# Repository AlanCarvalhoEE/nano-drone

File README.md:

# Nano Drone
NanoDrone is a very small drone, aimed to be very simple and cheap to build.
The project is under development and the first version should be manufactured soon.

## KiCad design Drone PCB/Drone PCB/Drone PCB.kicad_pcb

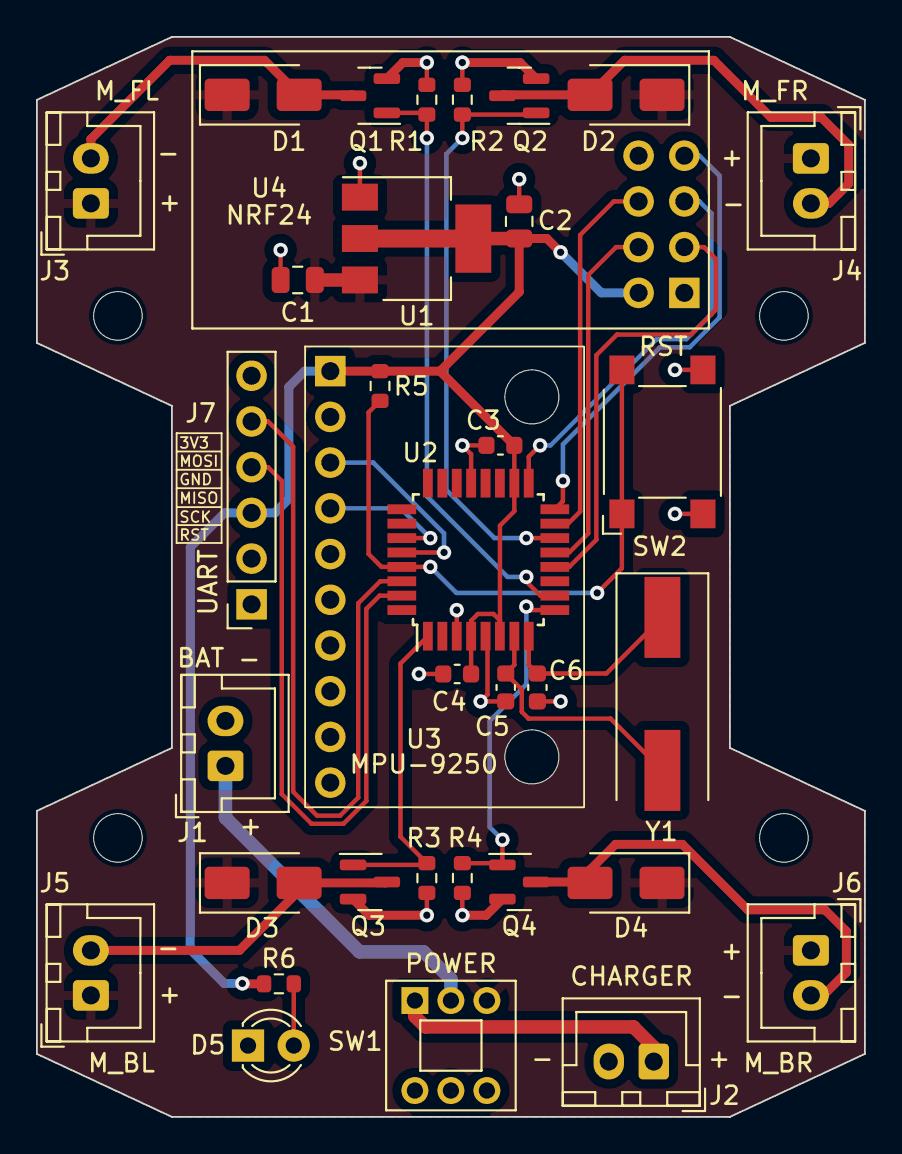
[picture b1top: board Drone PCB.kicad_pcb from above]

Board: 2 copper layers, 46.0 x 60.0 mm, 35 parts (0 on the bottom side), 26 nets.

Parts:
C1, C2: 10uF; C_0805_2012Metric
C3, C4: 100nF; C_0603_1608Metric
C5, C6: 22pF; C_0603_1608Metric
D1, D2, D3, D4: 1N4007; D_SMA
D5: LED; LED_D3.0mm_Clear
J1, J2, J3, J4, J5, J6: Conn_01x02_Socket; JST_XH_B2B-XH-A_1x02_P2.50mm_Vertical
J7: Conn_01x06_Socket; PinSocket_1x06_P2.54mm_Vertical
Q1, Q2, Q3, Q4: SI2302; SOT-23
R1, R2, R3, R4, R5: 10k; R_0603_1608Metric
R6: 220; R_0603_1608Metric
SW1: SW_SPDT; Toggle_Switch_SelfLocking_7x7
SW2: SW_Push; SW_SPST_Omron_B3FS-100xP
U1: AMS1117-3.3; SOT-223-3_TabPin2
U2: ATmega328P-A; TQFP-32_7x7mm_P0.8mm
U3: MPU-9250; MPU-9250_Module
U4: NRF24; NRF24_Module
Y1: 16MHz; Crystal_SMD_HC49-SD

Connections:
+3V3: C2.1, C3.2, C4.2, J7.3, R5.1, R6.1, U1.2 (VO), U2.4 (VCC), U2.6 (VCC), U2.18 (AVCC), U3.1 (VCC1), U4.2 (VCC)
CE: U2.12 (PB0), U4.3 (CE)
CSN: U2.13 (PB1), U4.4 (CSN)
GND: C1.2, C2.2, C3.1, C4.1, C5.2, C6.2, D5.1 (K), J1.2, J2.2, J7.6, Q1.2 (S), Q2.2 (S), Q3.2 (S), Q4.2 (S), R1.2, R2.2, R3.2, R4.2, SW2.2, U1.1 (GND), U2.3 (GND), U2.5 (GND), U2.21 (GND), U3.2 (GND), U4.1 (GND)
MISO: U2.16 (PB4), U4.7 (MISO)
MOSI: U2.15 (PB3), U4.6 (MOSI)
MOTOR_BL: Q3.1 (G), R3.1, U2.1 (PD3)
MOTOR_BR: Q4.1 (G), R4.1, U2.9 (PD5)
MOTOR_FL: Q1.1 (G), R1.1, U2.10 (PD6)
MOTOR_FR: Q2.1 (G), R2.1, U2.14 (PB2)
unnamed: D1.2 (A), J3.2, Q1.3 (D)
unnamed: D2.2 (A), J4.2, Q2.3 (D)
unnamed: D3.2 (A), J5.2, Q3.3 (D)
unnamed: D4.2 (A), J6.2, Q4.3 (D)
unnamed: D5.2 (A), R6.2
unnamed: J1.1, SW1.2 (B)
unnamed: J2.1, SW1.1 (A)
unnamed: C5.1, U2.7 (XTAL1/PB6), Y1.2
unnamed: C6.1, U2.8 (XTAL2/PB7), Y1.1
RESET: R5.2, SW2.1, U2.29 (~RESET/PC6)
RX: J7.5, U2.30 (PD0)
SCK: U2.17 (PB5), U4.5 (SCK)
SCL: U2.28 (PC5), U3.3 (SCL)
SDA: U2.27 (PC4), U3.4 (SDA)
TX: J7.4, U2.31 (PD1)
VCC: C1.1, D1.1 (K), D2.1 (K), D3.1 (K), D4.1 (K), J3.1, J4.1, J5.1, J6.1, SW1.3 (C), U1.3 (VI)

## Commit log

2024-02-12 PCB schematic done
2024-02-13 README file included
2024-02-13 PCB V1.0 layout done
2024-02-14 PCB layout improved
2024-02-21 3D model finished
2024-02-21 Images included
2024-02-21 gerber files generated
